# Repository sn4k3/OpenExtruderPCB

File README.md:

# OpenExtruderPCB
PCB to wireup 3D printer extruders

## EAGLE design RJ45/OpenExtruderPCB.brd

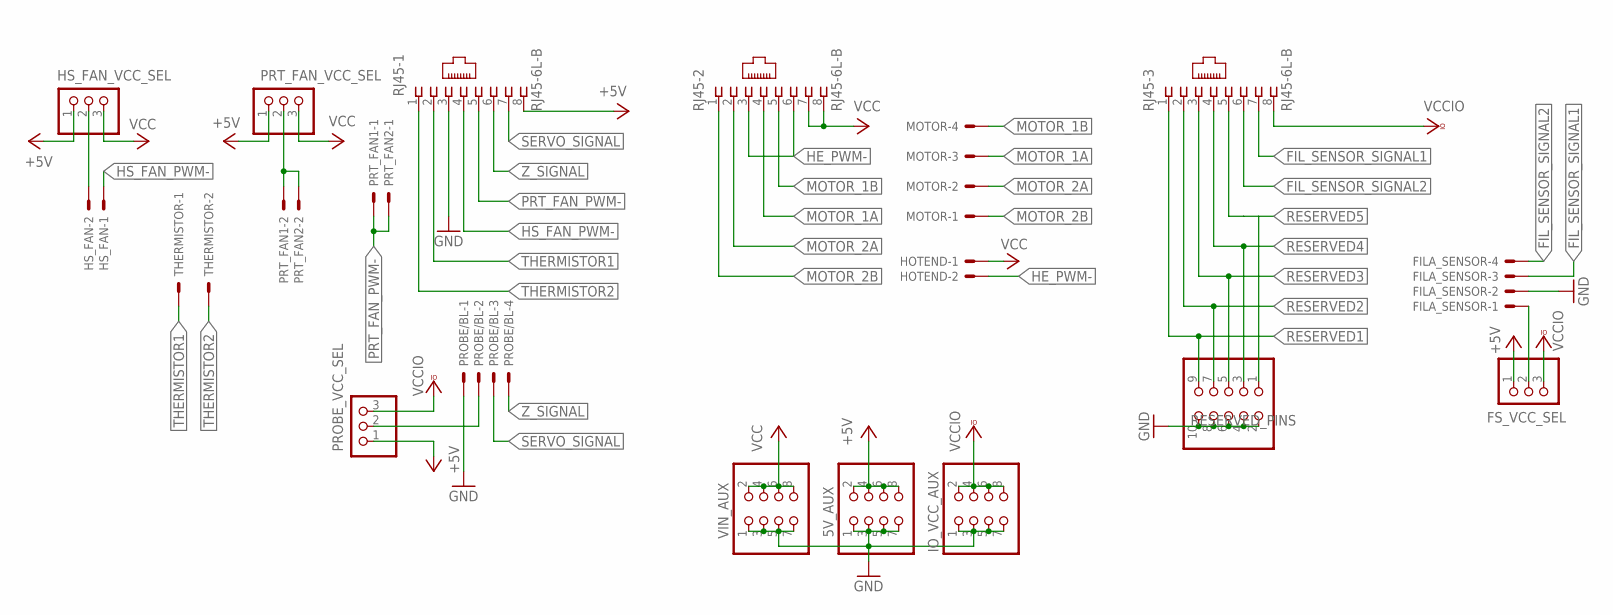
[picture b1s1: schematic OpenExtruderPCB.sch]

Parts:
5V_AUX: PINHD-2X4M; 2X04M
FILA_SENSOR: JST-XH-04-PIN-ROUND-PAD; JST-XH-04-PACKAGE-ROUND-PAD
FS_VCC_SEL: PINHD-1X3; 1X03
HOTEND: JST-XH-02-PIN-LONG-PAD; JST-XH-02-PACKAGE-LONG-PAD
HS_FAN: JST-XH-02-PIN-ROUND-PAD; JST-XH-02-PACKAGE-ROUND-PAD
HS_FAN_VCC_SEL: PINHD-1X3; 1X03
IO_VCC_AUX: PINHD-2X4M; 2X04M
MOTOR: JST-XH-04-PIN-LONG-PAD; JST-XH-04-PACKAGE-LONG-PAD
PROBE/BL: JST-XH-04-PIN-ROUND-PAD; JST-XH-04-PACKAGE-ROUND-PAD
PROBE_VCC_SEL: PINHD-1X3; 1X03
PRT_FAN1, PRT_FAN2: JST-XH-02-PIN-ROUND-PAD; JST-XH-02-PACKAGE-ROUND-PAD
PRT_FAN_VCC_SEL: PINHD-1X3; 1X03
RESERVED_PINS: PINHD-2X5M; 2X05M
RJ45-1, RJ45-2, RJ45-3: RJ45-6L-B; RJ45-NO-SHIELD
THERMISTOR: JST-XH-02-PIN-ROUND-PAD; JST-XH-02-PACKAGE-ROUND-PAD
VIN_AUX: PINHD-2X4M; 2X04M

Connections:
+5V: 5V_AUX.2, 5V_AUX.4, 5V_AUX.6, 5V_AUX.8, FS_VCC_SEL.1, HS_FAN_VCC_SEL.1, PROBE_VCC_SEL.1, PRT_FAN_VCC_SEL.1, RJ45-1.8
FIL_SENSOR_SIGNAL1: FILA_SENSOR.3, RJ45-3.7
FIL_SENSOR_SIGNAL2: FILA_SENSOR.4, RJ45-3.6
FS_VCC: FILA_SENSOR.1, FS_VCC_SEL.2
GND: 5V_AUX.1, 5V_AUX.3, 5V_AUX.5, 5V_AUX.7, FILA_SENSOR.2, IO_VCC_AUX.1, IO_VCC_AUX.3, IO_VCC_AUX.5, IO_VCC_AUX.7, PROBE/BL.1, RESERVED_PINS.2, RESERVED_PINS.4, RESERVED_PINS.6, RESERVED_PINS.8, RESERVED_PINS.10, RJ45-1.3, VIN_AUX.1, VIN_AUX.3, VIN_AUX.5, VIN_AUX.7
HE_PWM-: HOTEND.2, RJ45-2.3, RJ45-2.6
HS_FAN_PWM-: HS_FAN.1, RJ45-1.4
HS_FAN_VCC: HS_FAN.2, HS_FAN_VCC_SEL.2
MOTOR_1A: MOTOR.3, RJ45-2.4
MOTOR_1B: MOTOR.4, RJ45-2.5
MOTOR_2A: MOTOR.2, RJ45-2.2
MOTOR_2B: MOTOR.1, RJ45-2.1
PROBE_VCC: PROBE/BL.2, PROBE_VCC_SEL.2
PRT_FAN_PWM-: PRT_FAN1.1, PRT_FAN2.1, RJ45-1.5
PRT_FAN_VCC: PRT_FAN1.2, PRT_FAN2.2, PRT_FAN_VCC_SEL.2
RESERVED1: RESERVED_PINS.9, RJ45-3.1
RESERVED2: RESERVED_PINS.7, RJ45-3.2
RESERVED3: RESERVED_PINS.5, RJ45-3.3
RESERVED4: RESERVED_PINS.3, RJ45-3.4
RESERVED5: RESERVED_PINS.1, RJ45-3.5
SERVO_SIGNAL: PROBE/BL.3, RJ45-1.7
THERMISTOR1: RJ45-1.2, THERMISTOR.1
THERMISTOR2: RJ45-1.1, THERMISTOR.2
VCC: HOTEND.1, HS_FAN_VCC_SEL.3, PRT_FAN_VCC_SEL.3, RJ45-2.7, RJ45-2.8, VIN_AUX.2, VIN_AUX.4, VIN_AUX.6, VIN_AUX.8
VCCIO: FS_VCC_SEL.3, IO_VCC_AUX.2, IO_VCC_AUX.4, IO_VCC_AUX.6, IO_VCC_AUX.8, PROBE_VCC_SEL.3, RJ45-3.8
Z_SIGNAL: PROBE/BL.4, RJ45-1.6

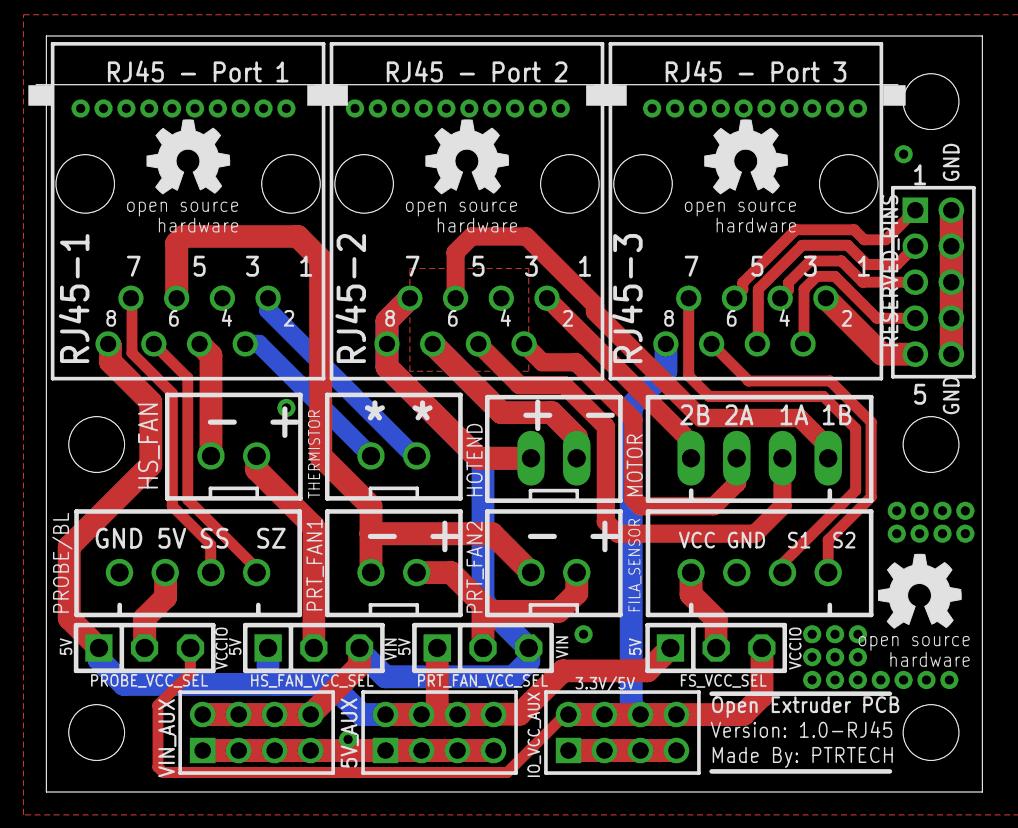
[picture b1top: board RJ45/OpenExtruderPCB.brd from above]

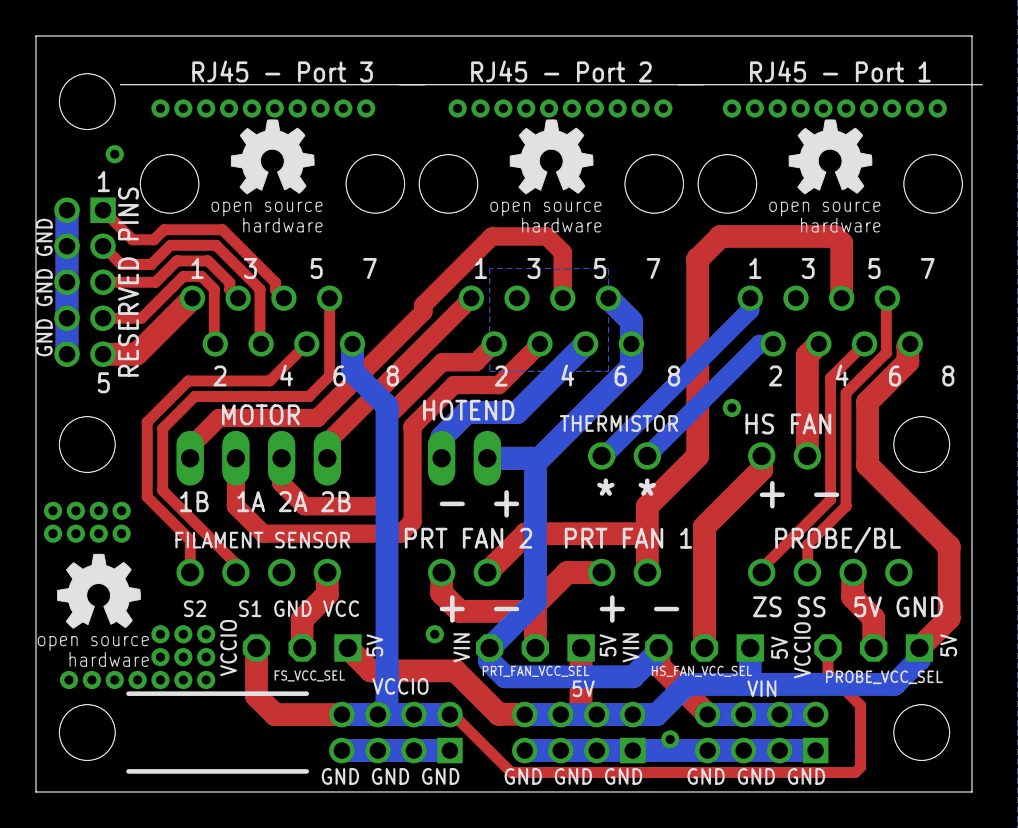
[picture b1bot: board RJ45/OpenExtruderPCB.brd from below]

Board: 2 copper layers, 52.6 x 42.0 mm, 27 parts (4 on the bottom side), 26 nets.

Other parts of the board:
U$1, U$2, U$3, U$4, U$5, U$6, U$7, U$8: OSHW_5MM

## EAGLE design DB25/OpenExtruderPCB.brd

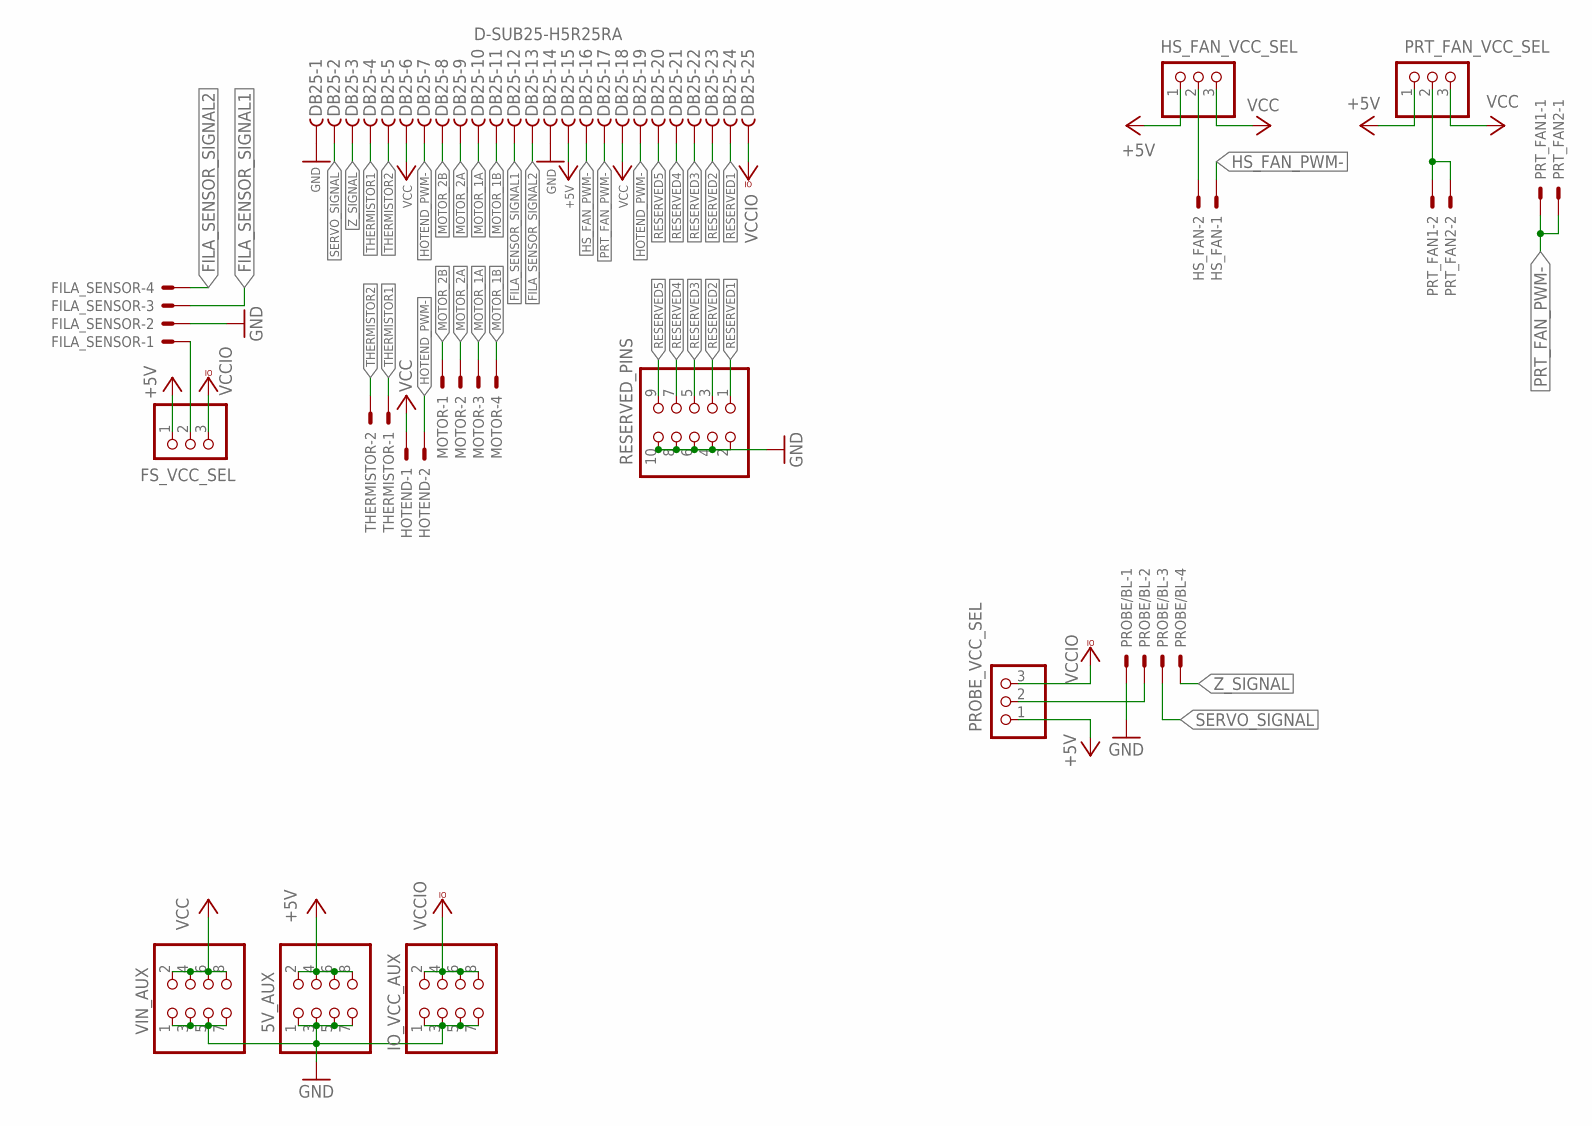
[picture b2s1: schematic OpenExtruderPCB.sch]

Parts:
5V_AUX: PINHD-2X4M; 2X04M
DB25: D-SUB25-H5R25RA; H5R25RA
FILA_SENSOR: JST-XH-04-PIN-ROUND-PAD; JST-XH-04-PACKAGE-ROUND-PAD
FS_VCC_SEL: PINHD-1X3; 1X03
HOTEND: JST-XH-02-PIN-LONG-PAD; JST-XH-02-PACKAGE-LONG-PAD
HS_FAN: JST-XH-02-PIN-ROUND-PAD; JST-XH-02-PACKAGE-ROUND-PAD
HS_FAN_VCC_SEL: PINHD-1X3; 1X03
IO_VCC_AUX: PINHD-2X4M; 2X04M
MOTOR: JST-XH-04-PIN-LONG-PAD; JST-XH-04-PACKAGE-LONG-PAD
PROBE/BL: JST-XH-04-PIN-ROUND-PAD; JST-XH-04-PACKAGE-ROUND-PAD
PROBE_VCC_SEL: PINHD-1X3; 1X03
PRT_FAN1, PRT_FAN2: JST-XH-02-PIN-ROUND-PAD; JST-XH-02-PACKAGE-ROUND-PAD
PRT_FAN_VCC_SEL: PINHD-1X3; 1X03
RESERVED_PINS: PINHD-2X5M; 2X05M
THERMISTOR: JST-XH-02-PIN-ROUND-PAD; JST-XH-02-PACKAGE-ROUND-PAD
VIN_AUX: PINHD-2X4M; 2X04M

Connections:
+5V: 5V_AUX.2, 5V_AUX.4, 5V_AUX.6, 5V_AUX.8, DB25.15, FS_VCC_SEL.1, HS_FAN_VCC_SEL.1, PROBE_VCC_SEL.1, PRT_FAN_VCC_SEL.1
FILA_SENSOR_SIGNAL1: DB25.12, FILA_SENSOR.3
FILA_SENSOR_SIGNAL2: DB25.13, FILA_SENSOR.4
FS_VCC: FILA_SENSOR.1, FS_VCC_SEL.2
GND: 5V_AUX.1, 5V_AUX.3, 5V_AUX.5, 5V_AUX.7, DB25.1, DB25.14, FILA_SENSOR.2, IO_VCC_AUX.1, IO_VCC_AUX.3, IO_VCC_AUX.5, IO_VCC_AUX.7, PROBE/BL.1, RESERVED_PINS.2, RESERVED_PINS.4, RESERVED_PINS.6, RESERVED_PINS.8, RESERVED_PINS.10, VIN_AUX.1, VIN_AUX.3, VIN_AUX.5, VIN_AUX.7
HOTEND_PWM-: DB25.7, DB25.19, HOTEND.2
HS_FAN_PWM-: DB25.16, HS_FAN.1
HS_FAN_VCC: HS_FAN.2, HS_FAN_VCC_SEL.2
MOTOR_1A: DB25.10, MOTOR.3
MOTOR_1B: DB25.11, MOTOR.4
MOTOR_2A: DB25.9, MOTOR.2
MOTOR_2B: DB25.8, MOTOR.1
PROBE_VCC: PROBE/BL.2, PROBE_VCC_SEL.2
PRT_FAN_PWM-: DB25.17, PRT_FAN1.1, PRT_FAN2.1
PRT_FAN_VCC: PRT_FAN1.2, PRT_FAN2.2, PRT_FAN_VCC_SEL.2
RESERVED1: DB25.24, RESERVED_PINS.1
RESERVED2: DB25.23, RESERVED_PINS.3
RESERVED3: DB25.22, RESERVED_PINS.5
RESERVED4: DB25.21, RESERVED_PINS.7
RESERVED5: DB25.20, RESERVED_PINS.9
SERVO_SIGNAL: DB25.2, PROBE/BL.3
THERMISTOR1: DB25.4, THERMISTOR.1
THERMISTOR2: DB25.5, THERMISTOR.2
VCC: DB25.6, DB25.18, HOTEND.1, HS_FAN_VCC_SEL.3, PRT_FAN_VCC_SEL.3, VIN_AUX.2, VIN_AUX.4, VIN_AUX.6, VIN_AUX.8
VCCIO: DB25.25, FS_VCC_SEL.3, IO_VCC_AUX.2, IO_VCC_AUX.4, IO_VCC_AUX.6, IO_VCC_AUX.8, PROBE_VCC_SEL.3
Z_SIGNAL: DB25.3, PROBE/BL.4

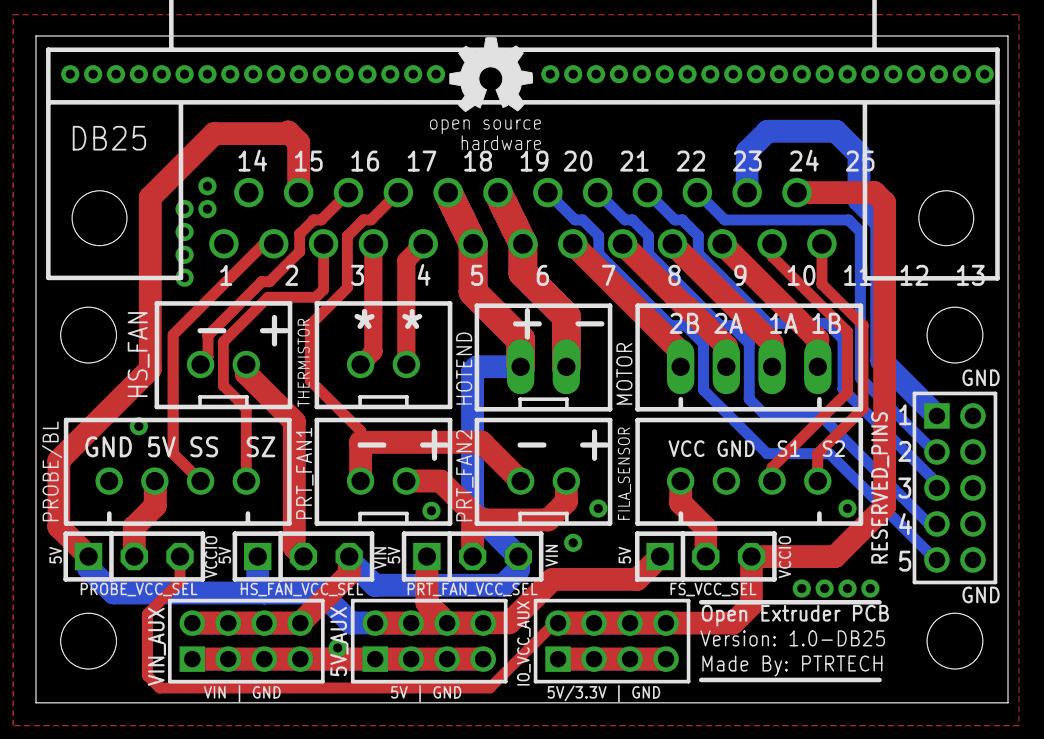
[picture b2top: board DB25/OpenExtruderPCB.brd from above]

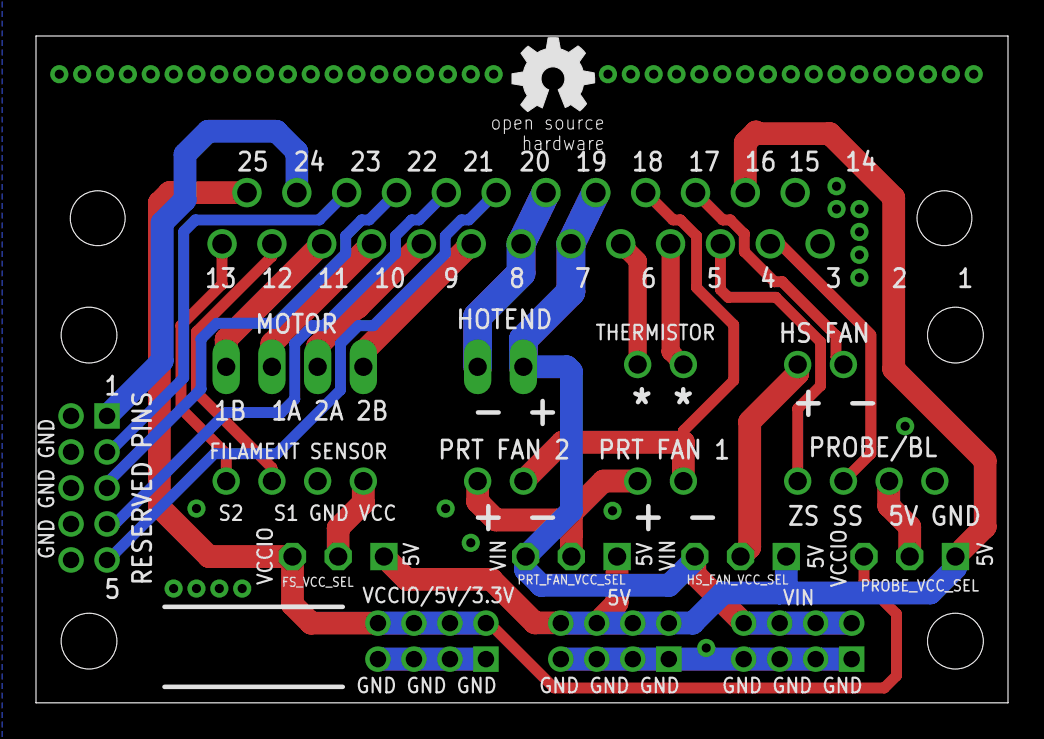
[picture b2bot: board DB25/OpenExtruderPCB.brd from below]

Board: 2 copper layers, 54.0 x 37.0 mm, 20 parts (2 on the bottom side), 26 nets.

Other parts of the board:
U$1, U$7, U$8: OSHW_5MM
